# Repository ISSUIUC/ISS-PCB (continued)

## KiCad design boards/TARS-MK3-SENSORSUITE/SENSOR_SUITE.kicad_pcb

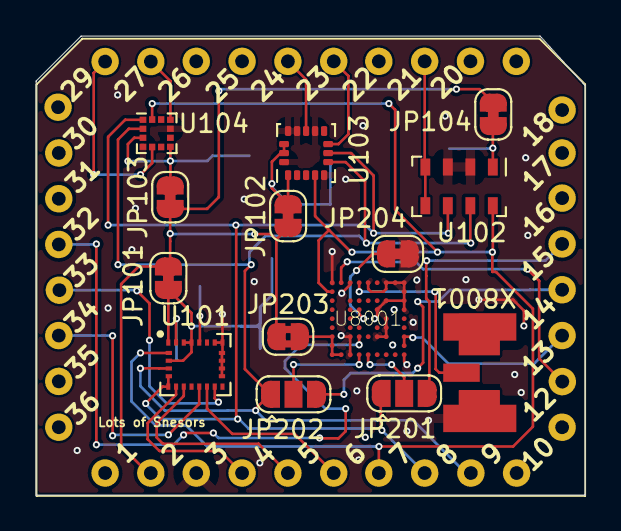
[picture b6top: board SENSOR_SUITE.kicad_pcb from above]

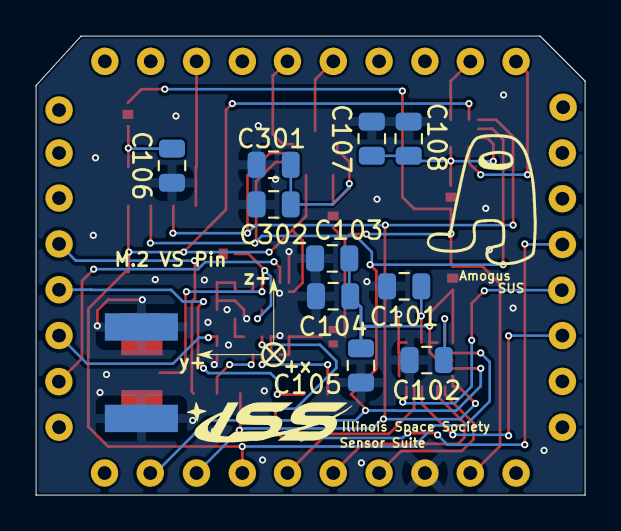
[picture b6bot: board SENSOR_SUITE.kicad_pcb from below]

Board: 2 copper layers, 30.5 x 25.5 mm, 25 parts (10 on the bottom side), 31 nets.

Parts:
C101: 10 nF; C_0805_2012Metric
C102, C103, C104: 100 nF; C_0805_2012Metric
C105: 10 uF; C_0805_2012Metric
C106, C107, C108: C_Small; C_0805_2012Metric
C301: 10uF; C_0805_2012Metric
C302: 0.1uF; C_0805_2012Metric
JP101, JP102, JP103, JP104, JP204: Jumper_NC_Small; SolderJumper-2_P1.3mm_Bridged_RoundedPad1.0x1.5mm
JP201, JP202: Jumper_3_Open; SolderJumper-3_P1.3mm_Open_RoundedPad1.0x1.5mm
JP203: Jumper_NC_Small; SolderJumper-2_P1.3mm_Bridged2Bar_RoundedPad1.0x1.5mm
U1: ISS_SENSOR_SUITE_V_1; General Sensor Module - 8x10 pin
U101: LSM9DS1; LGA-24L_3x3.5mm_P0.43mm
U102: MS5611-01BA; LGA-8_3x5mm_P1.25mm
U103: H3LIS331DL; LGA-16_3x3mm_P0.5mm_LayoutBorder3x5y
U104: KX122-1042; LGA-12_2x2mm_P0.5mm
U8001: ZOE-M8Q
X8001: SMACONNECTOR; uFL

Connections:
3V3: JP101.1, JP102.1, JP103.1, JP104.1, JP203.1, U1.2 (3V3)
/H3LIS331DL_CS: U1.23 (H3LIS331_CS), U103.8 (CS)
/H3LIS331DL_INT1: U1.24 (H3LIS331_INT1), U103.11 (INT1)
/KX122_CS: U1.27 (KX134_CS), U104.10 (~CS)
/KX122_INT1: U1.28 (KX134_INT1), U104.5 (INT1)
/LSM9_CS_AG: U1.4 (LSM9DS1_AG_CS), U101.7 (CS_A/G)
/LSM9_CS_M: U1.5 (LSM9DS1_M_CS), U101.8 (CS_M)
/LSM9_INT1_AG: U1.6 (LSM9DS1_AG_INT1), U101.11 (INT1_A/G)
/LSM9_INT2_AG: U1.33 (LSM9DS1_AG_INT2), U101.12 (INT2_A/G)
/LSM9_INT_M: U1.34 (LSM9DS1_M_INT), U101.10 (INT_M)
/MS5611_CS: U1.21 (MS5611_CS), U102.4 (CSB), U102.5 (CSB)
GND: C101.2, C102.2, C103.2, C104.2, C105.2, C106.1, C107.2, C108.2, C301.2, C302.2, JP204.1, U1.3 (GND), U101.14 (RES), U101.15 (RES), U101.16 (RES), U101.17 (RES), U101.18 (RES), U101.19 (GND), U102.2 (PS), U102.3 (GND), U103.5 (GND), U103.10 (GND), U103.12 (GND), U103.13 (GND), U103.16 (GND), U104.4 (TRIG), U104.9 (GND), U8001.P$A1 (A1_GND), U8001.P$A3 (A3_GND), U8001.P$A5 (A5_GND), U8001.P$A7 (A7_GND), U8001.P$A8 (A8_GND), U8001.P$A9 (A9_GND), U8001.P$B9 (B9_GND), U8001.P$C7 (C7_GND), U8001.P$C9 (C9_GND), U8001.P$D6 (D6_GND), U8001.P$D9 (D9_GND), U8001.P$E7 (E7_GND), U8001.P$F7 (F7_GND), U8001.P$G3 (G3_GND), U8001.P$G6 (G6_GND), U8001.P$G7 (G7_GND), U8001.P$J3 (J3_GND), U8001.P$J9 (J9_GND), X8001.GND1, X8001.GND2, X8001.GND3, X8001.GND4
GPS_EXTINT: U1.32 (ZOE_M8Q_INT), U8001.P$G4 (G4_PIO13/EXTINT)
unnamed: C101.1, U101.21 (CAP)
unnamed: C102.1, U101.24 (C1)
unnamed: C103.1, C104.1, C105.1, JP101.2, U101.1 (VDDIO), U101.3 (VDDIO), U101.22 (VDD), U101.23 (VDD)
unnamed: C106.2, JP104.2, U102.1 (VDD)
unnamed: C107.1, C108.1, JP103.2, U104.3 (IO_VDD), U104.7 (VDD)
unnamed: C301.1, C302.1, JP102.2, U103.1 (VDDIO), U103.14 (VDD), U103.15 (VDD)
unnamed: JP201.2 (C), U8001.P$J5 (J5_TXD/SPI_MISO)
unnamed: JP202.2 (C), U8001.P$J4 (J4_RXD/SPI_MOSI)
unnamed: JP203.2, U8001.P$G1 (G1_VCC), U8001.P$H1 (H1_VCC), U8001.P$J1 (J1_VCC), U8001.P$J2 (J2_VCC)
unnamed: JP204.2, U8001.P$D4 (D4_D_SEL)
unnamed: U8001.P$A4 (A4_RF_IN), X8001.ANTENNA (ANT)
SNS_SPI_MISO: JP201.1 (A), U1.8 (MISO0), U101.5 (SDO_A/G), U101.6 (SDO_M), U102.6 (SDO), U103.7 (SA0/SDO), U104.1 (SDO/ADDR)
SNS_SPI_MOSI: JP202.1 (A), U1.9 (MOSI0), U101.4 (SDA/SDI/SDO), U102.7 (SDI/SDA), U103.6 (SDA/SDI), U104.2 (SDI/SDA)
SNS_SPI_SCK: U1.7 (SCK0), U101.2 (SCL/SPC), U102.8 (SCLK), U103.4 (SCL/SCK), U104.12 (SCLK/SCL), U8001.P$B1 (B1_SCL/SPI_CLK)
SNS_UART_SDI: JP201.3 (B), U1.15 (TX0)
SNS_UART_SDO: JP202.3 (B), U1.14 (RX0)
VBAT0: U1.13 (VBACKUP), U8001.P$G9 (G9_RESERVED), U8001.P$H9 (H9_V_BCKP)
ZOE_M8Q_CS: U1.12 (ZOE_M8Q_CS), U8001.P$A2 (A2_SDA/SPI_CS_N)

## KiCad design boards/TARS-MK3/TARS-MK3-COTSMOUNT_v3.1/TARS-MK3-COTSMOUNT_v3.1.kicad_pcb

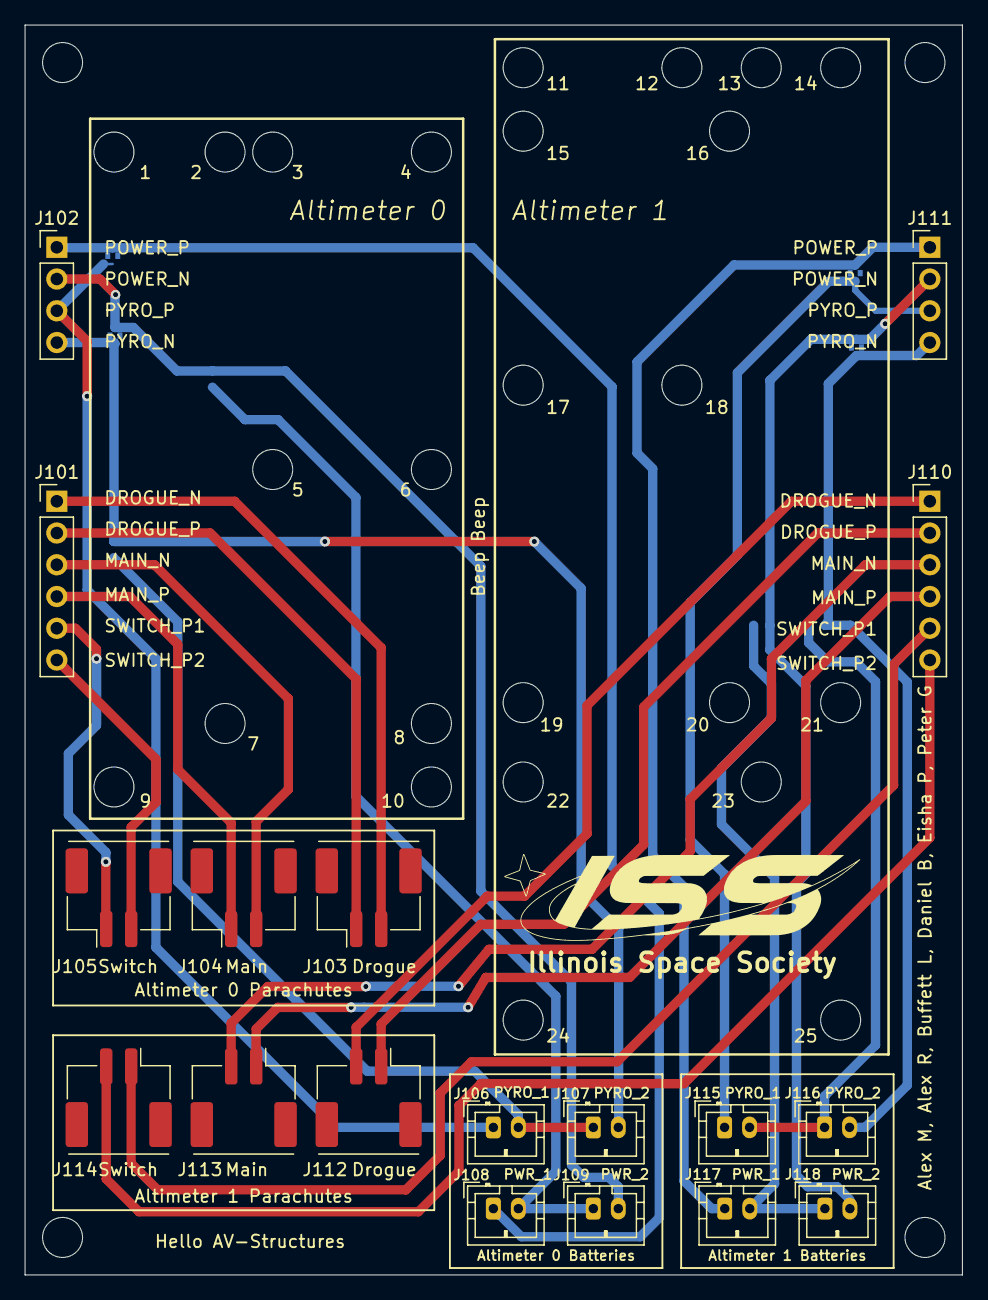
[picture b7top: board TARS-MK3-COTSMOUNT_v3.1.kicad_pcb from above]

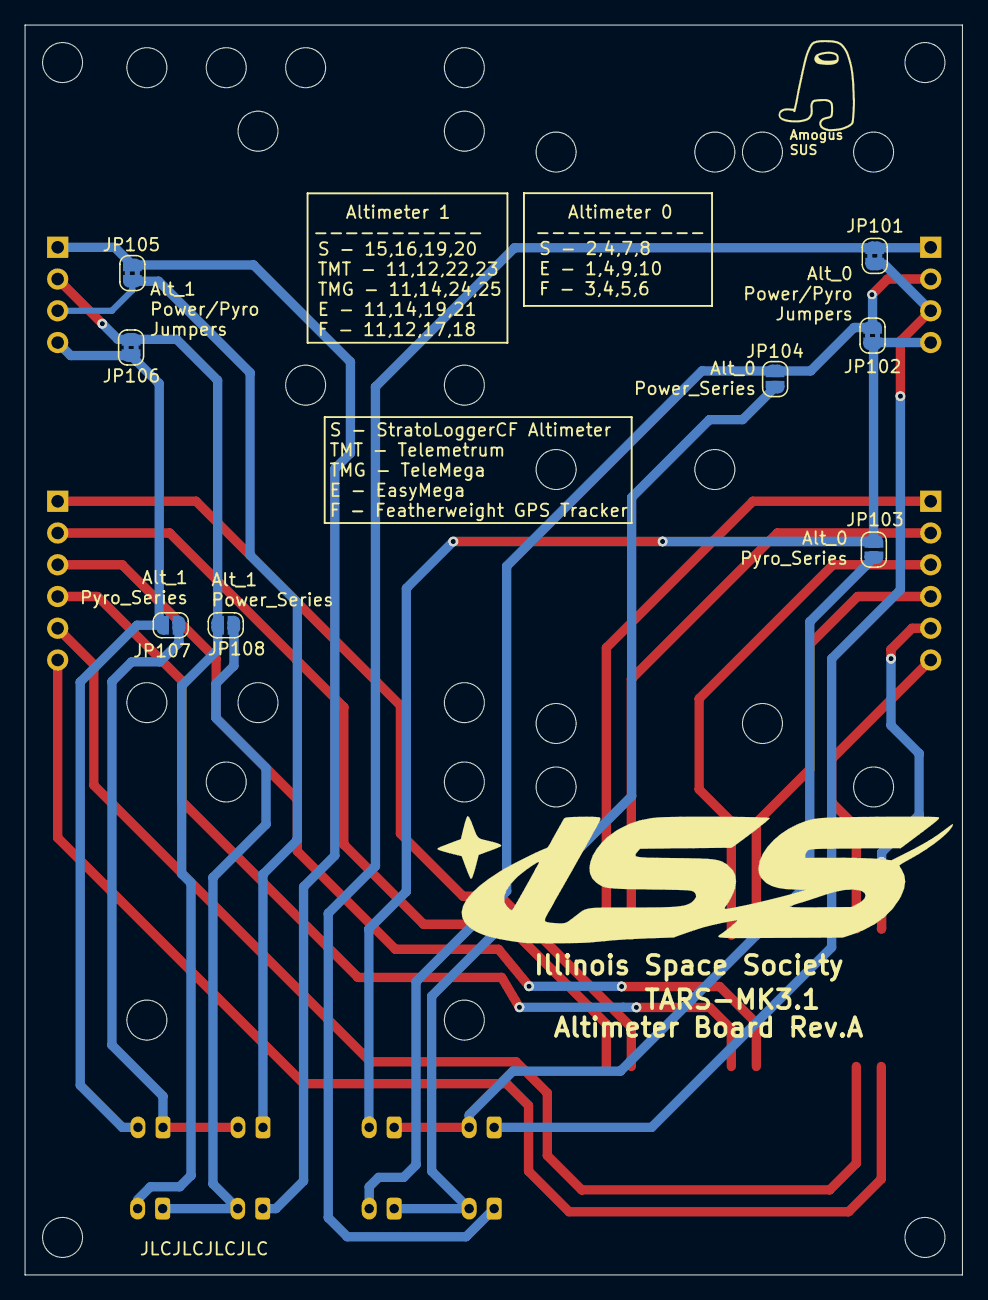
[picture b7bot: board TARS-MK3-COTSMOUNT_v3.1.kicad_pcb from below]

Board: 2 copper layers, 75.0 x 100.0 mm, 26 parts (8 on the bottom side), 24 nets.

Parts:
J101, J110: Conn_01x06_Male; PinHeader_1x06_P2.54mm_Vertical
J102, J111: Conn_01x04_Male; PinHeader_1x04_P2.54mm_Vertical
J103, J104, J105, J112, J113, J114: Conn_01x02_Female; Molex_CLIK-Mate_502443-0270_1x02-1MP_P2.00mm_Vertical
J106, J107, J108, J109, J115, J116, J117, J118: Conn_01x02_Female; JST_PH_B2B-PH-K_1x02_P2.00mm_Vertical
JP101, JP102, JP105, JP106: Jumper_2_Bridged; SolderJumper-2_P1.3mm_Bridged2Bar_RoundedPad1.0x1.5mm
JP103, JP104, JP107, JP108: Jumper_2_Open; SolderJumper-2_P1.3mm_Open_RoundedPad1.0x1.5mm

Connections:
/ALT_0_DROGUE_N: J101.1, J103.2
/ALT_0_DROGUE_P: J101.2, J103.1
/ALT_0_MAIN_N: J101.3, J104.2
/ALT_0_MAIN_P: J101.4, J104.1
/ALT_0_SWITCH_P1: J101.5, J105.1
/ALT_0_SWITCH_P2: J101.6, J105.2
/ALT_1_DROGUE_N: J110.1, J112.2
/ALT_1_DROGUE_P: J110.2, J112.1
/ALT_1_MAIN_N: J110.3, J113.2
/ALT_1_MAIN_P: J110.4, J113.1
/ALT_1_SWITCH_P1: J110.5, J114.1
/ALT_1_SWITCH_P2: J110.6, J114.2
ALT_0_POWER_N: J102.2, J109.2, JP102.1 (A), JP104.1 (A)
ALT_0_POWER_P: J102.1, J108.1, JP101.1 (A)
ALT_0_PYRO_N: J102.4, J107.2, JP102.2 (B), JP103.1 (A)
ALT_0_PYRO_P: J102.3, J106.1, JP101.2 (B)
ALT_1_POWER_N: J111.2, J118.2, JP106.1 (A), JP108.1 (A)
ALT_1_POWER_P: J111.1, J117.1, JP105.1 (A)
ALT_1_PYRO_N: J111.4, J116.2, JP106.2 (B), JP107.1 (A)
ALT_1_PYRO_P: J111.3, J115.1, JP105.2 (B)
unnamed: J106.2, J107.1, JP103.2 (B)
unnamed: J108.2, J109.1, JP104.2 (B)
unnamed: J115.2, J116.1, JP107.2 (B)
unnamed: J117.2, J118.1, JP108.2 (B)

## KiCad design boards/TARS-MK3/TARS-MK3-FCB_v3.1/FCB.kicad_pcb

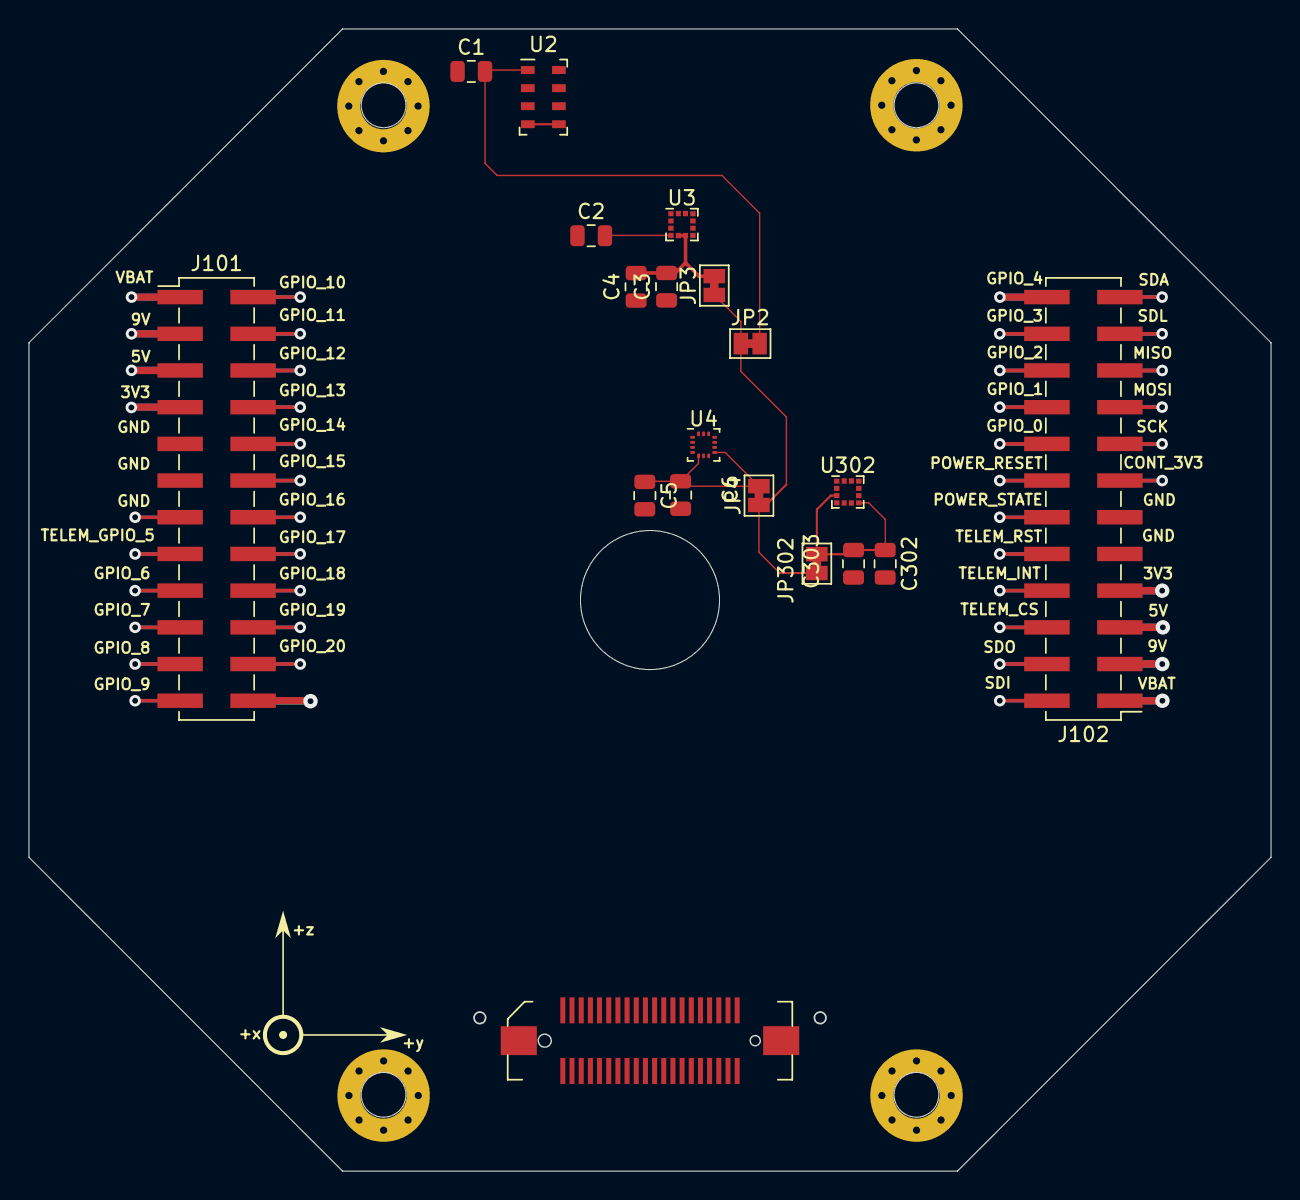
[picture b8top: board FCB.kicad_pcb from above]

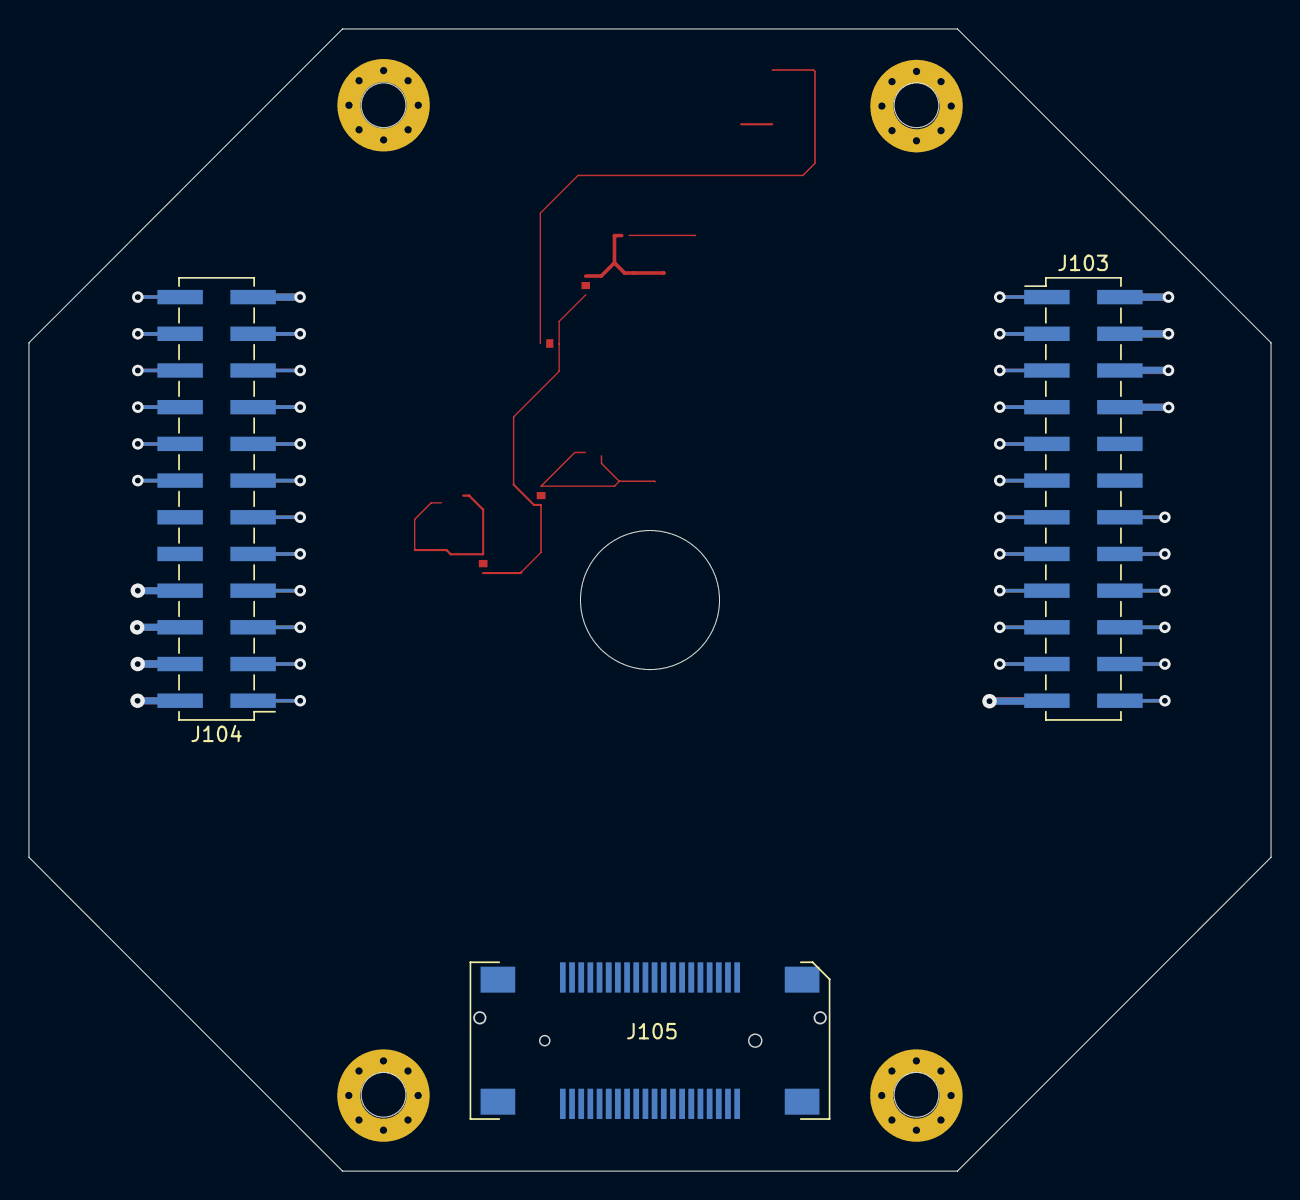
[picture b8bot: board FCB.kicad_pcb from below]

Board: 2 copper layers, 86.0 x 79.1 mm, 22 parts (3 on the bottom side), 52 nets.

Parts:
C1, C302, C303: 100nF; C_0805_2012Metric
C2, C4: 100nf; C_0805_2012Metric
C3: 1uf; C_0805_2012Metric
C5, C6: 100 nF; C_0805_2012Metric
J101, J102, J103, J104: Conn_02x12_Odd_Even; PinHeader_2x12_P2.54mm_Vertical_SMD
J105: Receptacle; 2091680401
J106: 536270474
JP2, JP302: Jumper_NC_Small; SolderJumper-2_P1.3mm_Bridged_Pad1.0x1.5mm
JP3, JP4: Jumper_2_Bridged; SolderJumper-2_P1.3mm_Bridged_Pad1.0x1.5mm
U2: MS5611-01BA; LGA-8_3x5mm_P1.25mm
U3: LIS3MDL; LGA-12_2x2mm_P0.5mm
U4: LSM6DSRXTR; LGA-14_2x2mm_P0.35mm_LayoutBorder3x4y
U302: KX134-1211; LGA-12_2x2mm_P0.5mm

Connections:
6V_AC_SERVO1: J102.24, J104.23
6V_AC_SERVO2: J101.24, J103.23
/3V3: J101.7, J102.7, J103.8, J104.8
/5V: J101.5, J102.5, J103.6, J104.6
/9V: J101.3, J102.3, J103.4, J104.4
/B2B_GPIO_8: J101.21, J103.22
/B2B_GPIO_9: J101.23, J103.24
/B2B_GPIO_10: J101.2, J103.1
/B2B_GPIO_11: J101.4, J103.3
/B2B_GPIO_12: J101.6, J103.5
/B2B_GPIO_13: J101.8, J103.7
/B2B_GPIO_14: J101.10, J103.9
/B2B_GPIO_15: J101.12, J103.11
/B2B_GPIO_16: J101.14, J103.13
/B2B_GPIO_17: J101.16, J103.15
/B2B_GPIO_18: J101.18, J103.17
/B2B_GPIO_19: J101.20, J103.19
/B2B_GPIO_20: J101.22, J103.21
/B2B_I2C_SCL: J102.21, J104.22
/B2B_I2C_SDA: J102.23, J104.24
/B2B_SPI_MISO: J102.19, J104.20
/B2B_SPI_MOSI: J102.17, J104.18
/B2B_SPI_SCK: J102.15, J104.16
/B2B_UART_SDI: J102.2, J104.1
/B2B_UART_SDO: J102.4, J104.3
/CONT_3V3: J102.13, J104.14
/CONT_GND: J101.13, J103.14
/GND: J101.9, J101.11, J102.9, J102.11, J103.10, J103.12, J104.10, J104.12
/POWER_RESET: J102.14, J104.13
/POWER_STATE: J102.12, J104.11
/SENSORS/3V3: JP2.1 (A), JP3.1 (A), JP4.1 (A), JP302.1 (A)
/SENSORS/MS5611_CS: U2.4 (CSB), U2.5 (CSB)
/SENSORS/SPI_MISO: U2.6 (SDO), U3.9 (SDO/SA1), U4.1 (SDO/SA0), U302.1 (SDO/ADDR)
/SENSORS/SPI_MOSI: U3.11 (SDA/SDI/SDO), U4.14 (SDA), U302.2 (SDI/SDA)
/SENSORS/SPI_SCK: U2.8 (SCLK), U3.1 (SCL/SPC), U4.13 (SCL), U302.12 (SCLK/SCL)
/SERVO1: J101.17, J103.18
/SERVO2: J101.19, J103.20
/TELEM_CS: J102.6, J104.5
/TELEM_GPIO_1: J102.16, J104.15
/TELEM_GPIO_2: J102.18, J104.17
/TELEM_GPIO_3: J102.20, J104.19
/TELEM_GPIO_4: J102.22, J104.21
/TELEM_GPIO_5: J101.15, J103.16
/TELEM_INT: J102.8, J104.7
/TELEM_RST: J102.10, J104.9
/VBAT: J101.1, J102.1, J103.2, J104.2
GND: C1.1, C2.1, C3.1, C4.1, C5.2, C6.2, C302.2, C303.1, U2.2 (PS), U2.3 (GND), U3.2 (Res), U3.3 (GND), U3.12 (Res), U4.2 (SDx), U4.3 (SCx), U4.6 (GND), U4.7 (GND), U302.4 (TRIG), U302.9 (GND)
unnamed: C1.2, JP2.2 (B), U2.1 (VDD)
unnamed: C2.2, U3.4 (C1)
unnamed: C3.2, C4.2, JP3.2 (B), U3.5 (Vdd), U3.6 (Vdd_IO)
unnamed: C5.1, C6.1, JP4.2 (B), U4.5 (Vdd_IO), U4.8 (Vdd)
unnamed: C302.1, C303.2, JP302.2 (B), U302.3 (IO_VDD), U302.7 (VDD)
